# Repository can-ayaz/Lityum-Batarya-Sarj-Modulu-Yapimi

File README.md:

# Lityum-Batarya-Sarj-Modulu-Yapimi
**Lityum Batarya Şarj Modülü Yapımı**

Lityum pil şarjı için özel üretilmiş MCP73831  adlı bu entegreyi sizlerle paylaşmak istedim. Lİ-ON ve Lİ-PO bataryaları artık  5 pasif eleman ile şarj edebilirsiniz. Çalışması yer açısından çok büyük avantaj. Giriş için  6V kadar gerilim uygulanabiliyor ve usb’den rahatlıkla kullanılabilecek şekilde tasarladım, Çizimleri indirip kendinize göre modifiye edebilirsiniz. Son rakamı 12345 olarak istenen çıkış gerilimi seçenekleri mevcut, 500 mA’e kadar ayarlanabilir çıkış akımı veriyor, hızlı şarj modunda çalıştırılabilir, li-po ve li-on pillerin şarj karakteristiği olan sabit akım sonra sabit gerilim modunu kendi ayarlıyor. Şarj bitince şarjı kesiyor  ve pil haftalarca şarjda bırakılabilir, 4.50 volta kadar şarj bitirme gerilimi isteyen pilleri rahatlıkla Şarj edebilirsiniz, sarj durumu hakkında  led ile uyarı alabilir veya bu çıkışı küçük bir ayarla lojik olarakta kullanabilirsiniz.

**Daha Fazlası için; https://canayazblog.wordpress.com/2018/06/22/arduino-otto-robot-yapimi/**

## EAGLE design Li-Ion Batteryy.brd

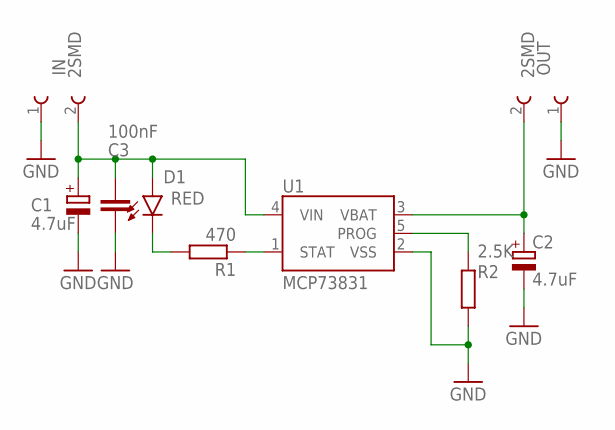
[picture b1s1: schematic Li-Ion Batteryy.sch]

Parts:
C1, C2: 4.7uF; SMC_A
C3: 100nF; C0805
D1: RED; LED-1206
IN: 2SMD
OUT: 2SMD
R1: 470; R1206
R2: 2.5K; R1206
U1: MCP73831; SOT23-5

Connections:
GND: C1.-, C2.-, C3.2, IN.1, OUT.1, R2.2, U1.2 (VSS)
unnamed: R1.1, U1.1 (STAT)
unnamed: D1.C, R1.2
unnamed: R2.1, U1.5 (PROG)
VBAT: C2.+, OUT.2, U1.3 (VBAT)
VIN: C1.+, C3.1, D1.A, IN.2, U1.4 (VIN)

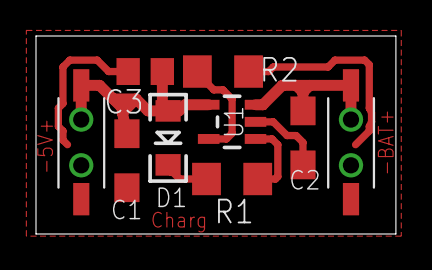
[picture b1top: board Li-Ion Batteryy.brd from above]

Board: 2 copper layers, 20.0 x 11.0 mm, 9 parts (0 on the bottom side), 6 nets.

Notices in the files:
parts and their libraries:
SparkFun-LED: Licensing: Creative Commons ShareAlike 4.0 International - https://creativecommons.org/licenses/by-sa/4.0
Wuerth_Elektronik_eiCan_Pin_: Copyright: Würth Elektronik
